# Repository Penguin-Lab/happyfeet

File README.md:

# happyfeet
O Happy é um robô móvel dotado de sensores e controlado por um Arduino! Com este robô, temos a possibilidade de realizar tarefas em um ambiente inteligente! O objetivo é a criação de um espaço inteligente no IFES Guarapari e o primeiro passo é ter uma plataforma robótica que consiga executar tarefas móveis neste espaço.

# Estrutura física
A estrutura física do robô é composta por dois andares feitos de acrílico. Os arquivos de CAD com os cortes e furos estão na pasta CAD deste projeto.
As peças projetadas em 3D foram impressas utilizando PLA e podem ser encontradas na pasta Pecas_3d deste projeto.

## Placas de circuito impresso
No projeto, foram desenvolvidas duas placas de circuito:
* Shield para o Arduino Mega e sensores
* Placa para a ESP8266 12

## Componentes eletrônicos
Os componentes eletrônicos embarcados no robô e equipamentos utilizados são:
* Controlador
  * Arduino Mega
* Módulo Wi-fi
  * ESP8266 12E
  * Conversor step down 5V/3,3V
  * Display OLED
* Motores
  * Motores 6V com encoder
  * Módulo Ponte H L298n
* Sensores
  * FPV Camera System 3-IN-1 antenna Cloverleaf
  * Módulo ultrassom HC-SR04
* Bateria
  * Bateria Zippy 1100mAh 2s 6,6v
  * Carregador de bateria iMax B6 80W

# Software
Na pasta de códigos, há o código de programação do Arduino Mega, da ESP8266 12 (podendo-se utilizar o NodeMCU no lugar), e um exemplo em Python de controlador de posição final com offset. Esse código em Python que se comunica com o robô por meio do protocolo MQTT, utilizando como broker o Mosquitto.

# Exemplos
## Exemplo para conferir a odometria vinda do robô (terminal do ubuntu):
`mosquitto_sub -t happy/odometry`

## Exemplo para conferir as velocidades publicadas no tópico que o robô consome (terminal do ubuntu):
`mosquitto_sub -t happy/velocities`

## Exemplo para publicar velocidades no tópico que o robô consome (terminal do ubuntu):
`mosquitto_pub -t happy/velocities -m <1;100.00;-20.00>`

## Exemplo para executar o controlador de posição final com offset (terminal do ubuntu):
`python controller.py`

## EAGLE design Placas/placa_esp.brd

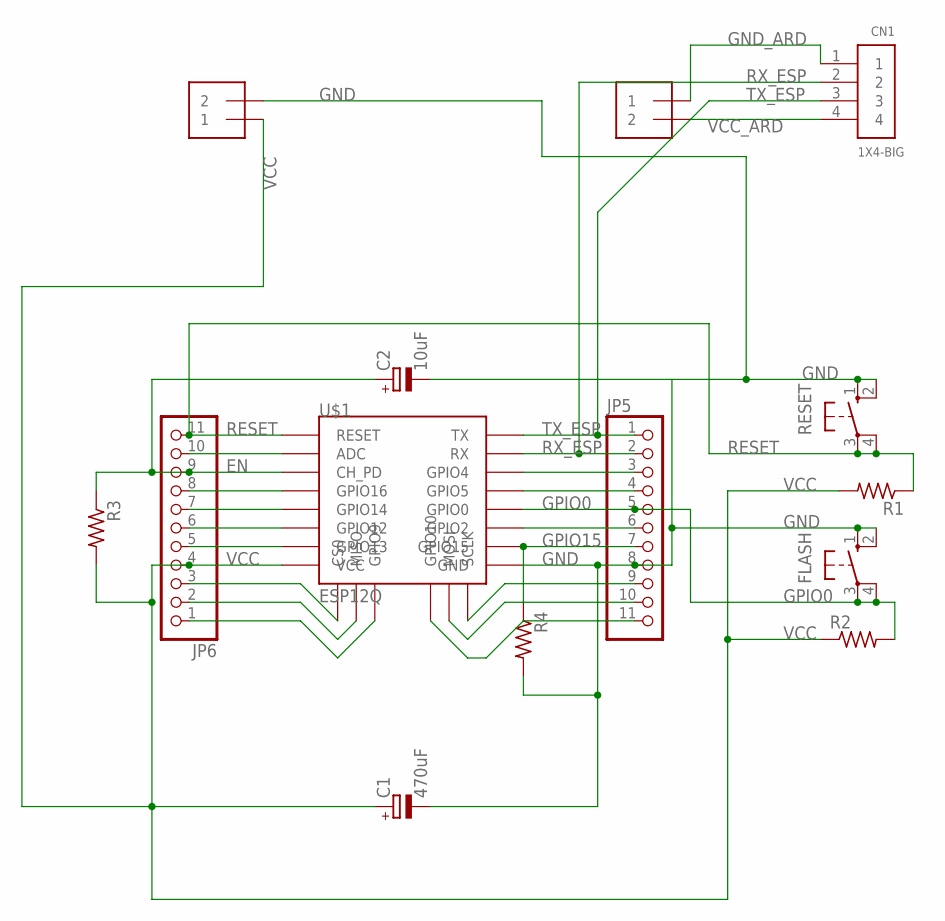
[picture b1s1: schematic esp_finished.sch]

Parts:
C1: 470uF; E5-5
C2: 10uF; E3,5-8
CN1: 1X4-BIG; 1X04-BIG
FLASH: 10-XX; B3F-10XX
J1, J2: 1X2-3.5MM
JP5, JP6: PINHD-1X11; 1X11
R1, R2, R3, R4: R-US_0204/5; 0204/5
RESET: 10-XX; B3F-10XX
U$1: ESP12Q

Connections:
EN: C2.+, JP6.9, R3.1, U$1.CH_PD
GND: C1.-, C2.-, FLASH.1 (S), FLASH.2 (S1), J2.2, JP5.8, R4.2, RESET.1 (S), RESET.2 (S1), U$1.GND
GND_ARD: CN1.1, J1.1
GPIO0: FLASH.3, FLASH.4 (P1), JP5.5, R2.2, U$1.GPIO0
GPIO15: JP5.7, R4.1, U$1.GPIO15
unnamed: JP5.9, U$1.SCLK
unnamed: JP5.10, U$1.MOSI
unnamed: JP5.11, U$1.GPIO10
unnamed: JP6.3, U$1.CS0
unnamed: JP6.2, U$1.MISO
unnamed: JP6.1, U$1.GPIO9
unnamed: JP6.10, U$1.ADC
unnamed: JP6.8, U$1.GPIO16
unnamed: JP6.7, U$1.GPIO14
unnamed: JP6.6, U$1.GPIO12
unnamed: JP6.5, U$1.GPIO13
unnamed: JP5.3, U$1.GPIO4
unnamed: JP5.4, U$1.GPIO5
unnamed: JP5.6, U$1.GPIO2
RESET: JP6.11, R1.1, RESET.3, RESET.4 (P1), U$1.RESET
RX_ESP: CN1.2, JP5.2, U$1.RX
TX_ESP: CN1.3, JP5.1, U$1.TX
VCC: C1.+, J2.1, JP6.4, R1.2, R2.1, R3.2, U$1.VCC
VCC_ARD: CN1.4, J1.2

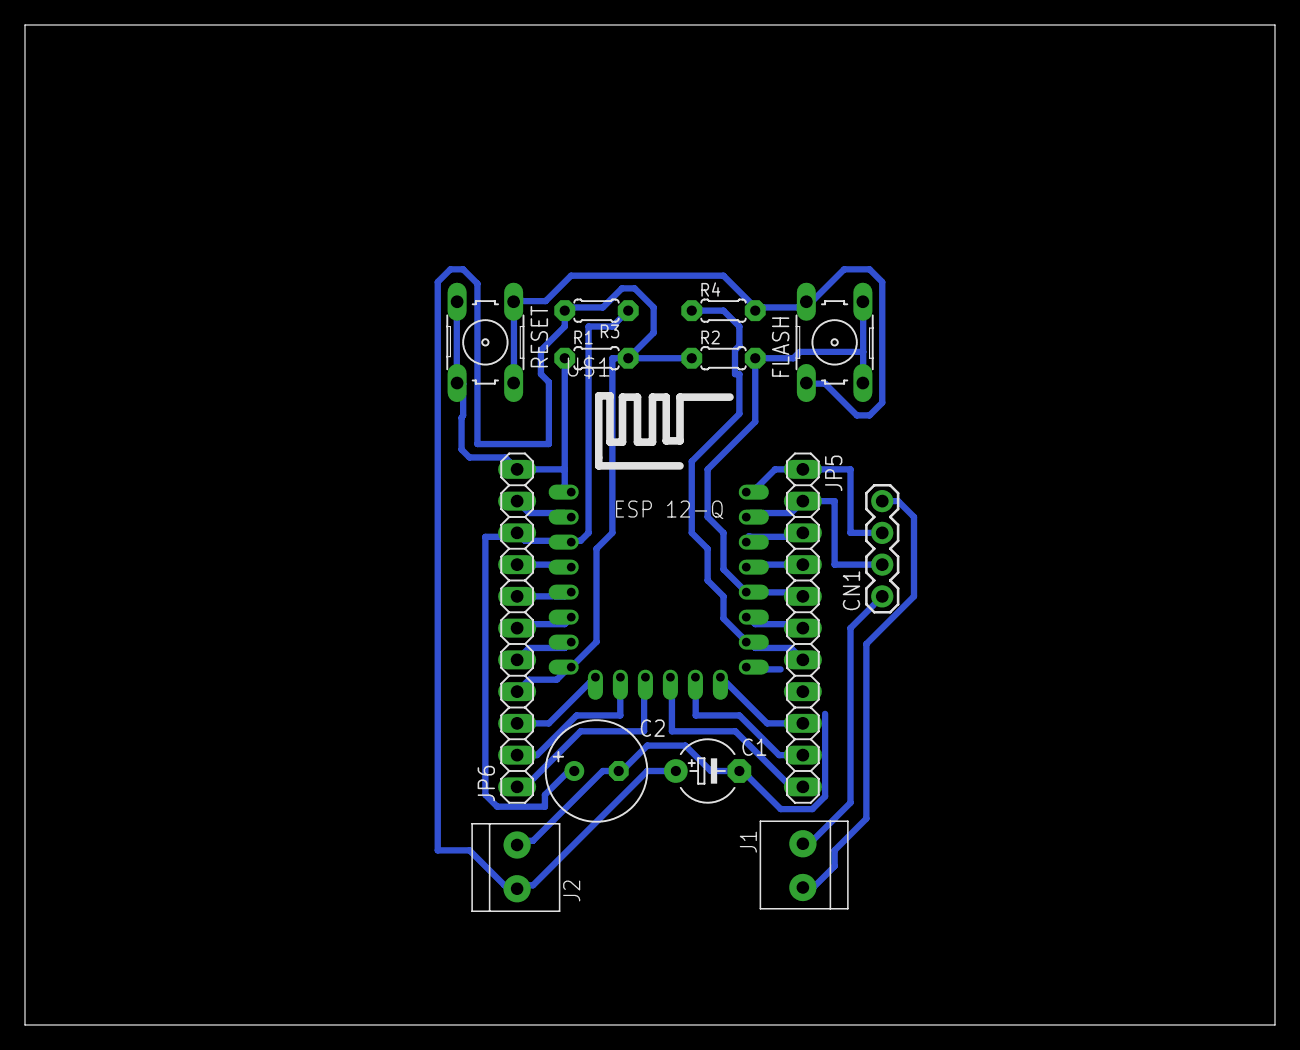
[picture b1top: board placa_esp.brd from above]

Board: 2 copper layers, 100.0 x 80.0 mm, 14 parts (0 on the bottom side), 24 nets.

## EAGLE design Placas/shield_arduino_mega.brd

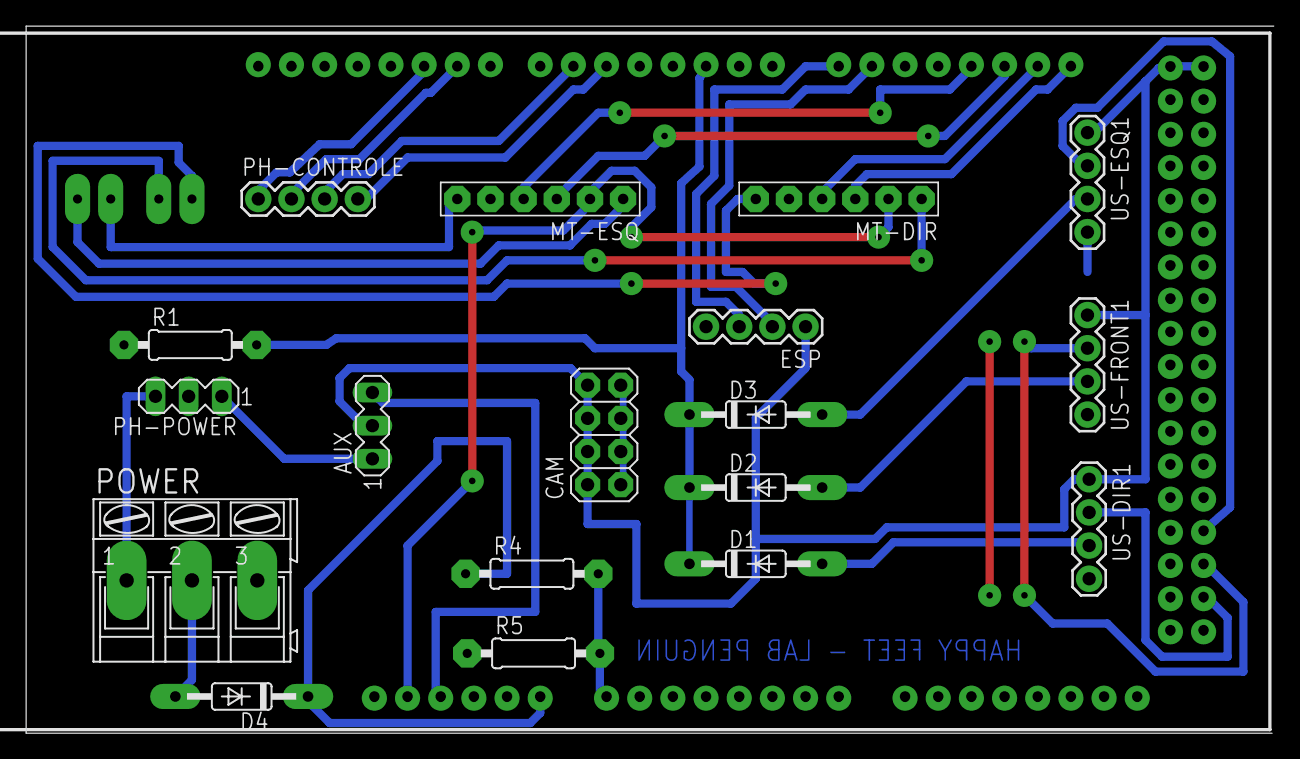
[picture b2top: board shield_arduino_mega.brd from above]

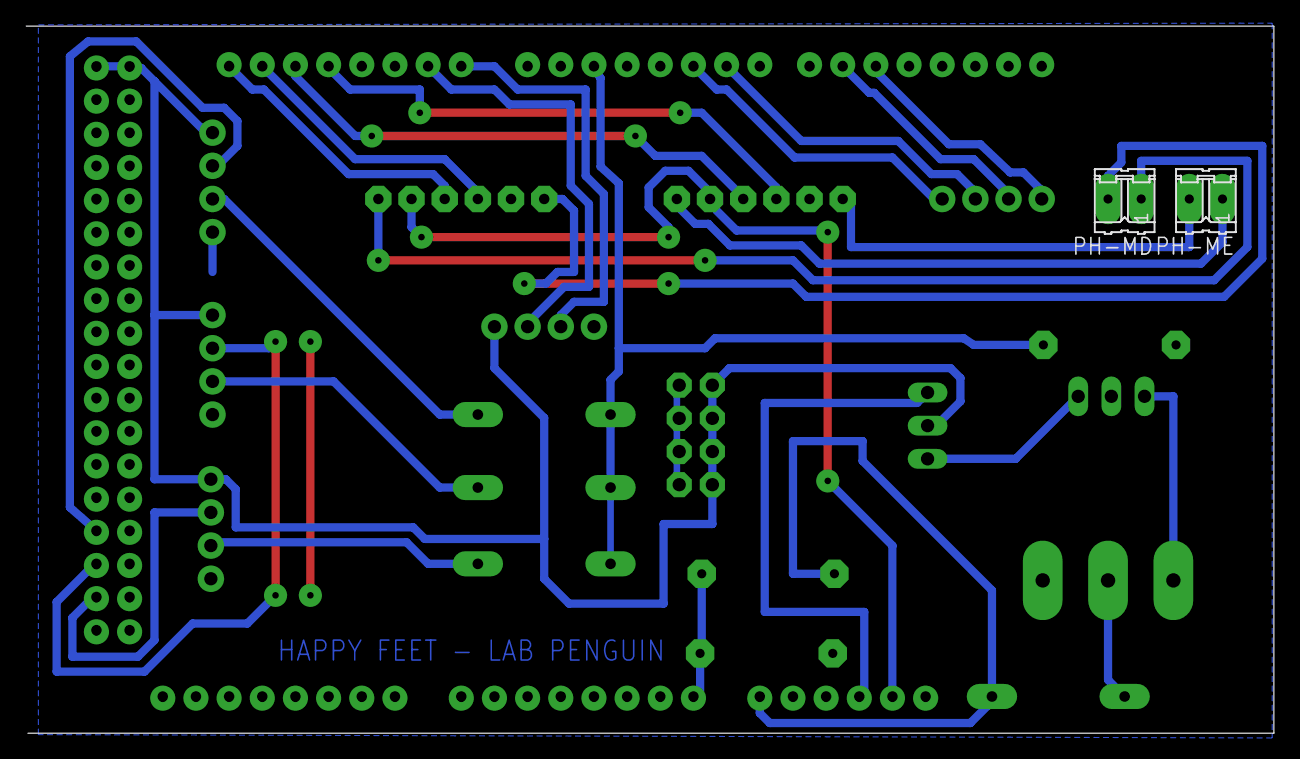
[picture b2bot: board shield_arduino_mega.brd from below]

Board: 2 copper layers, 95.6 x 54.1 mm, 21 parts (2 on the bottom side), 30 nets.

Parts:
AUX: MA03-1
CAM: 2X04
D1, D2, D3, D4: 1N4148; DO35-10
ESP: 1X4-BIG; 1X04-BIG
MT-DIR: 1X06-BIG-EDIT
MT-ESQ: 1X06-BIG-EDIT
PH-CONTROLE: 1X4-BIG; 1X04-BIG
PH-MD: 02P
PH-ME: 02P
PH-POWER: MA03-1
POWER: AK300/3
R1, R5: 10k; 0207/10
R4: 3.9k; 0207/10
U$1: MEGA_DEVICE; MEGAOUTLINE
US-DIR1: 1X4-BIG; 1X04-BIG
US-ESQ1: 1X4-BIG; 1X04-BIG
US-FRONT1: 1X4-BIG; 1X04-BIG

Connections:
2: D1.C, D2.C, D3.C, R1.2, U$1.2
3V3: MT-DIR.2, MT-ESQ.2, U$1.3V3
5: PH-CONTROLE.4, U$1.5
5V: AUX.2, CAM.2, CAM.4, CAM.6, CAM.8, ESP.1, U$1.GND@4, U$1.GND@5, US-DIR1.1, US-ESQ1.1, US-FRONT1.1
5V-ARD: AUX.3, U$1.5V
5V-H: AUX.1, PH-POWER.1
6: PH-CONTROLE.3, U$1.6
9: PH-CONTROLE.2, U$1.9
10: PH-CONTROLE.1, U$1.10
18: MT-ESQ.4, U$1.18
19: MT-ESQ.3, U$1.19
20: MT-DIR.4, U$1.20
21: MT-DIR.3, U$1.21
49: U$1.49, US-ESQ1.2
51: U$1.51, US-FRONT1.2
53: U$1.53, US-DIR1.2
A0: R4.2, R5.2, U$1.A0
ARD-RX: ESP.2, U$1.15
ARD-TX: ESP.3, U$1.14
ECHO: D3.A, US-ESQ1.3
ECHOO: D2.A, US-FRONT1.3
ECHOOOOOO: D1.A, US-DIR1.3
GND: CAM.1, CAM.3, CAM.5, CAM.7, ESP.4, MT-DIR.5, MT-ESQ.5, PH-POWER.2, POWER.3, R1.1, R5.1, U$1.GND@1, U$1.GND@2, U$1.GND@3, US-DIR1.4, US-ESQ1.4, US-FRONT1.4
MD+: MT-DIR.1, PH-MD.1
MD-: MT-DIR.6, PH-MD.2
ME+: MT-ESQ.1, PH-ME.1
ME-: MT-ESQ.6, PH-ME.2
unnamed: D4.A, POWER.2
VIN-ARD: D4.C, R4.1, U$1.VIN
VIN-PH: PH-POWER.3, POWER.1

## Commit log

2020-03-22 Add files via upload
    Arquivos de CAD da estrutura física do robô
2020-03-22 Add files via upload
    Peças em 3D (STL) impressas em PLA
2020-03-22 Add files via upload
    Placas de circuito impresso do shield para Arduino Mega e da ESP8266 12
2020-03-22 Rename Placa final.brd to shield_arduino_mega.brd
2020-03-22 Rename Placa final.sch to shield_arduino_mega.sch
2020-03-22 Rename esp_finished.brd to placa_esp.brd
2020-03-22 Rename esp_finished.sch to placa_esp.sch
2020-03-22 Add files via upload
    Códigos de programação do Arduino Mega e da ESP8266 12, além de um exemplo de código em Python que utiliza o protocolo de comunicação MQTT (Mosquitto broker)
2020-03-22 Add files via upload
    fotos
2020-03-23 Rename controller_ard.py to controller_ard v1.1.py
    Code for Raspberry
